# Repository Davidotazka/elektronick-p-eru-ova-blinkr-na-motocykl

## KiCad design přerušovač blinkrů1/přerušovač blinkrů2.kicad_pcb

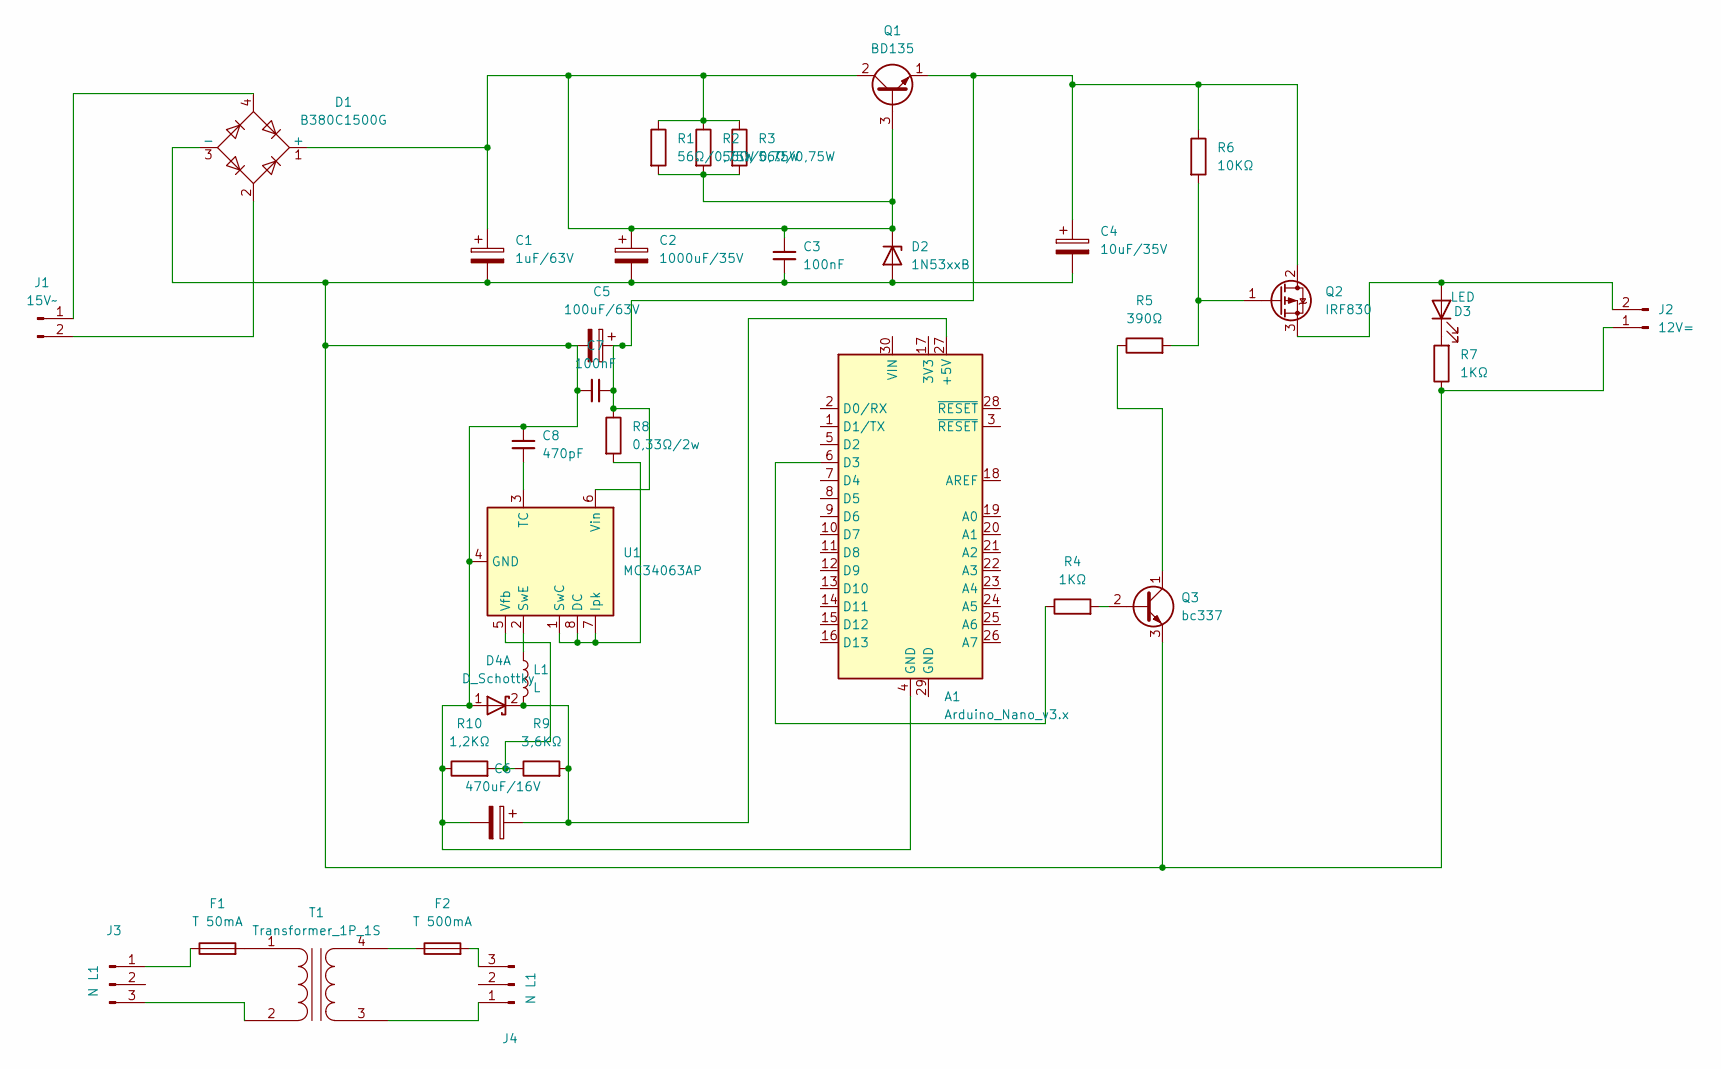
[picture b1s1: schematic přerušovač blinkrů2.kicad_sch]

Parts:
A1: Arduino_Nano_v3.x; Arduino_Nano
C1: 1uF/63V; CP_Radial_D5.0mm_P2.00mm
C2: 1000uF/35V; CP_Radial_D10.0mm_P5.00mm
C3, C7: 100nF; C_Disc_D10.5mm_W5.0mm_P5.00mm
C4: 10uF/35V; CP_Radial_D8.0mm_P3.80mm
C5: 100uF/63V; CP_Radial_D8.0mm_P3.80mm
C6: 470uF/16V; CP_Radial_D8.0mm_P3.80mm
C8: 470pF; C_Disc_D10.5mm_W5.0mm_P5.00mm
D1: B380C1500G; Diode_Bridge_Round_D9.0mm
D2: 1N53xxB; D_DO-201_P15.24mm_Horizontal
D3: LED; LED_D5.0mm
D4: D_Schottky; D_DO-35_SOD27_P7.62mm_Horizontal
F1: T 50mA; Fuseholder_Clip-5x20mm_Littelfuse_445-030_Inline_P20.50x5.2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
F2: T 500mA; Fuseholder_Clip-5x20mm_Littelfuse_445-030_Inline_P20.50x5.2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
J1: 15V~; TerminalBlock_MaiXu_MX126-5.0-02P_1x02_P5.00mm
J2: 12V=; TerminalBlock_MaiXu_MX126-5.0-02P_1x02_P5.00mm
J3, J4: N L1; TerminalBlock_MaiXu_MX126-5.0-03P_1x03_P5.00mm
L1: L; L_Radial_D12.5mm_P7.00mm_Fastron_09HCP
Q1: BD135; TO-126-3_Vertical
Q2: IRF830; TO-220-3_Vertical
Q3: bc337; TO-92_Inline
R1, R2, R3: 56Ω/0,75W; R_Axial_DIN0207_L6.3mm_D2.5mm_P10.16mm_Horizontal
R4, R7: 1KΩ; R_Axial_DIN0207_L6.3mm_D2.5mm_P10.16mm_Horizontal
R5: 390Ω; R_Axial_DIN0207_L6.3mm_D2.5mm_P10.16mm_Horizontal
R6: 10KΩ; R_Axial_DIN0207_L6.3mm_D2.5mm_P10.16mm_Horizontal
R8: 0,33Ω/2w; R_Axial_DIN0207_L6.3mm_D2.5mm_P10.16mm_Horizontal
R9: 3,6KΩ; R_Axial_DIN0207_L6.3mm_D2.5mm_P10.16mm_Horizontal
R10: 1,2KΩ; R_Axial_DIN0207_L6.3mm_D2.5mm_P10.16mm_Horizontal
T1: Transformer_1P_1S; Transformer_Zeming_ZMPT101K
U1: MC34063AP; DIP-8_W7.62mm

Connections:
unnamed: A1.27 (+5V), C6.1, D4.2 (K), L1.2, R9.2
unnamed: A1.6 (D3), R4.1
unnamed: C1.1, C2.1, C3.1, D1.1 (+), D2.1 (K), Q1.2 (C), Q1.3 (B), R1.1, R1.2, R2.1, R2.2, R3.1, R3.2
unnamed: A1.4 (GND), C1.2, C2.2, C3.2, C4.2, C5.2, C6.2, C7.2, C8.1, D1.3 (-), D2.2 (A), D4.1 (A), J2.1, Q3.3 (E), R7.1, R10.1, U1.4 (GND)
unnamed: D3.2 (A), J2.2, Q2.3 (S)
unnamed: D3.1 (K), R7.2
unnamed: D1.4, J1.1
unnamed: D1.2, J1.2
unnamed: F1.1, J3.1
unnamed: J3.3, T1.2 (AB)
unnamed: J4.1, T1.3 (SA)
unnamed: F2.2, J4.3
unnamed: C4.1, C5.1, C7.1, Q1.1 (E), Q2.2 (D), R6.1, R8.1, U1.6 (Vin)
unnamed: Q2.1 (G), R5.2, R6.2
unnamed: Q3.2 (B), R4.2
unnamed: Q3.1 (C), R5.1
unnamed: F1.2, T1.1 (AA)
unnamed: F2.1, T1.4 (SB)
unnamed: R8.2, U1.1 (SwC), U1.7 (Ipk), U1.8 (DC)
unnamed: L1.1, U1.2 (SwE)
unnamed: C8.2, U1.3 (TC)
unnamed: R9.1, R10.2, U1.5 (Vfb)

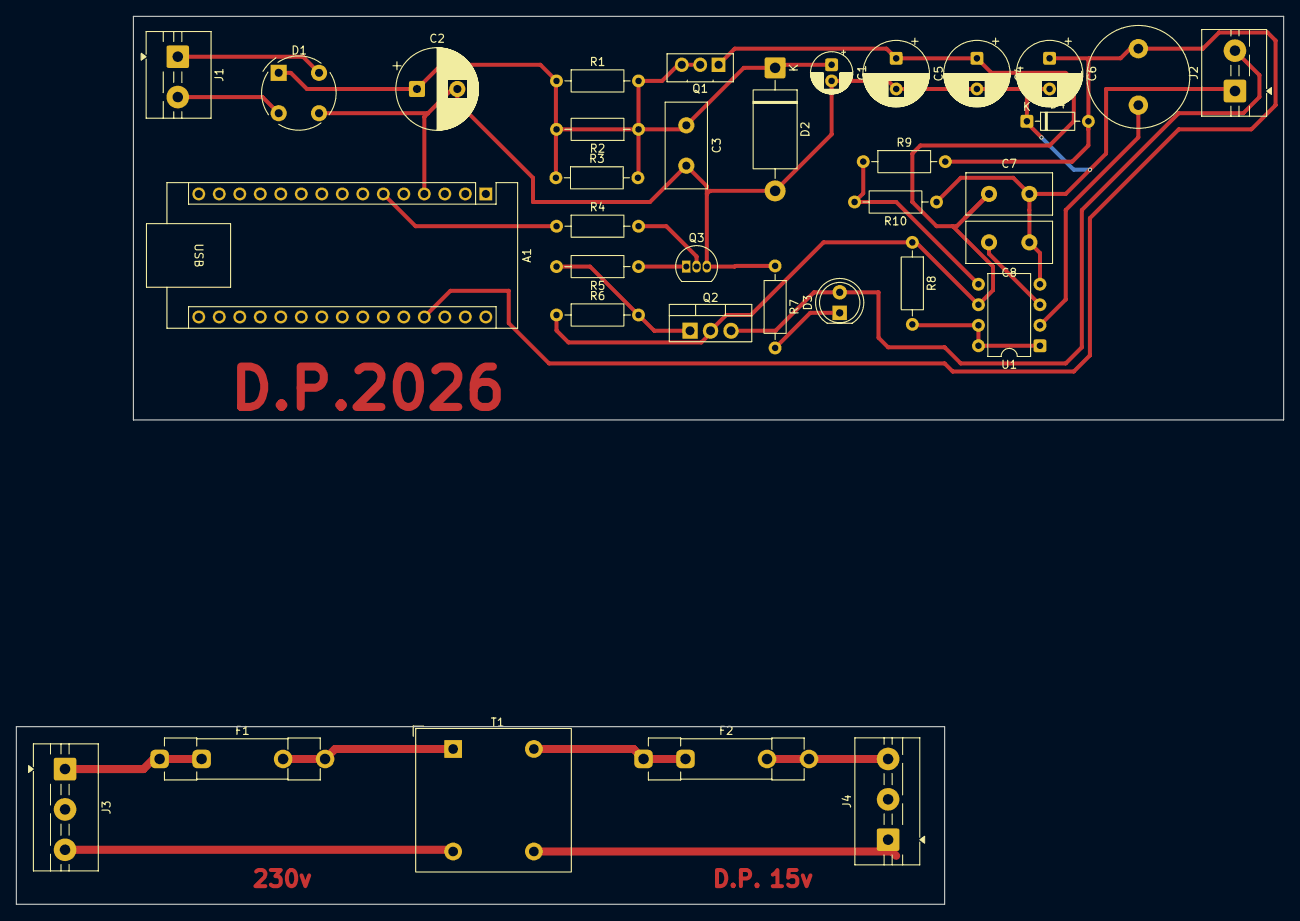
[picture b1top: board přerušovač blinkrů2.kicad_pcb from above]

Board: 2 copper layers, 142.5 x 50.0 mm, 35 parts (0 on the bottom side), 22 nets.
